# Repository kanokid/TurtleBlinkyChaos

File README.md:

# TurtleBlinkyChaos
This is a PCB design in the shape of a turtle that uses three astable multivibrators and SPDT switches to create a chaos blinky with two LEDs for the eyes that blink on and off, on and off, in kind of a random order depending on how you flip the switches.

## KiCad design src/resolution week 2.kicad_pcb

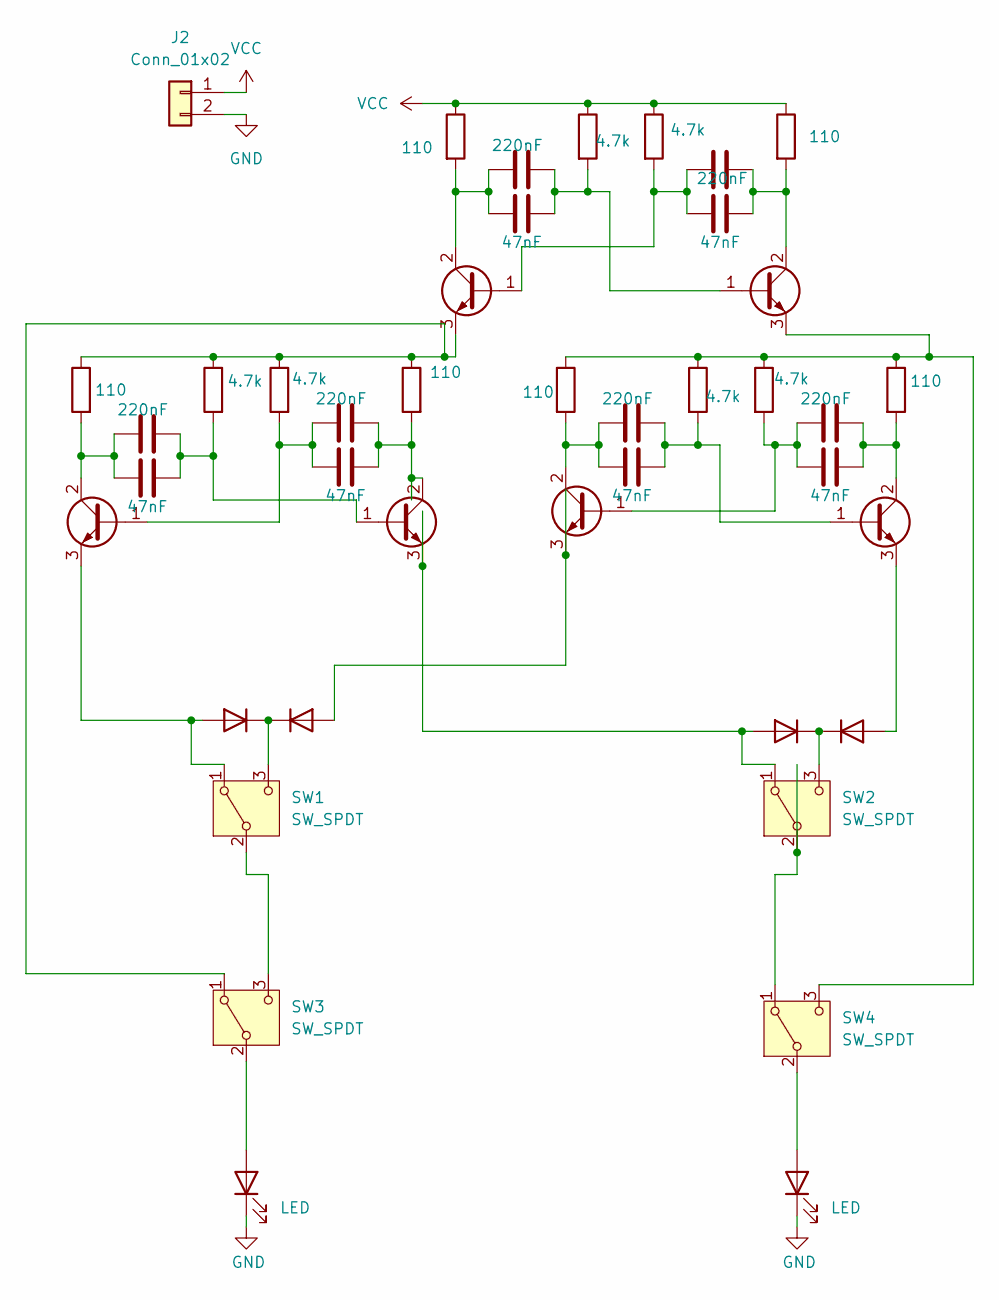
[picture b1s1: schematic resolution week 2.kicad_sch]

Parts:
C1, C2, C3, C4, C5, C6: 220nF; C_Disc_D5.0mm_W2.5mm_P5.00mm
C7, C8, C9, C10, C11, C12: 47nF; C_Disc_D5.0mm_W2.5mm_P5.00mm
D1, D3, D5, D6: D; D_DO-35_SOD27_P7.62mm_Horizontal
D4, D7: LED; LED_D5.0mm
J2: Conn_01x02; PinHeader_1x02_P2.54mm_Vertical
Q1, Q2, Q3, Q4, Q5, Q6: Q_NPN_BCE; TO-92L_Inline_Wide
R1, R4, R5, R8, R9, R12: 110; R_Axial_DIN0204_L3.6mm_D1.6mm_P7.62mm_Horizontal
R2, R3, R6, R7, R10, R11: 4.7k; R_Axial_DIN0204_L3.6mm_D1.6mm_P7.62mm_Horizontal
SW1, SW2, SW3, SW4: SW_SPDT; SS12D10G5

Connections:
GND: D4.1 (K), D7.1 (K), J2.2
unnamed: D1.2 (A), Q6.3 (E)
unnamed: D1.1 (K), D3.1 (K), SW1.3 (C)
unnamed: D3.2 (A), Q4.3 (E), SW1.1 (A)
unnamed: D4.2 (A), SW3.2 (B)
unnamed: D5.2 (A), Q5.3 (E)
unnamed: D5.1 (K), D6.1 (K), SW2.3 (C)
unnamed: D6.2 (A), Q3.3 (E), SW2.1 (A)
unnamed: D7.2 (A), SW4.2 (B)
unnamed: C1.1, C12.2, Q1.1 (B), R2.2
unnamed: C2.1, C11.2, Q1.2 (C), R4.2
unnamed: Q1.3 (E), R9.1, R10.1, R11.1, R12.1, SW4.3 (C)
unnamed: C2.2, C11.1, Q2.1 (B), R3.2
unnamed: C1.2, C12.1, Q2.2 (C), R1.2
unnamed: Q2.3 (E), R5.1, R6.1, R7.1, R8.1, SW3.1 (A)
unnamed: C4.1, C7.2, Q3.1 (B), R7.2
unnamed: C3.1, C8.2, Q3.2 (C), R5.2
unnamed: C3.2, C8.1, Q4.1 (B), R6.2
unnamed: C4.2, C7.1, Q4.2 (C), R8.2
unnamed: C6.1, C9.2, Q5.1 (B), R11.2
unnamed: C5.1, C10.2, Q5.2 (C), R9.2
unnamed: C5.2, C10.1, Q6.1 (B), R10.2
unnamed: C6.2, C9.1, Q6.2 (C), R12.2
unnamed: SW1.2 (B), SW3.3 (C)
unnamed: SW2.2 (B), SW4.1 (A)
VCC: J2.1, R1.1, R2.1, R3.1, R4.1

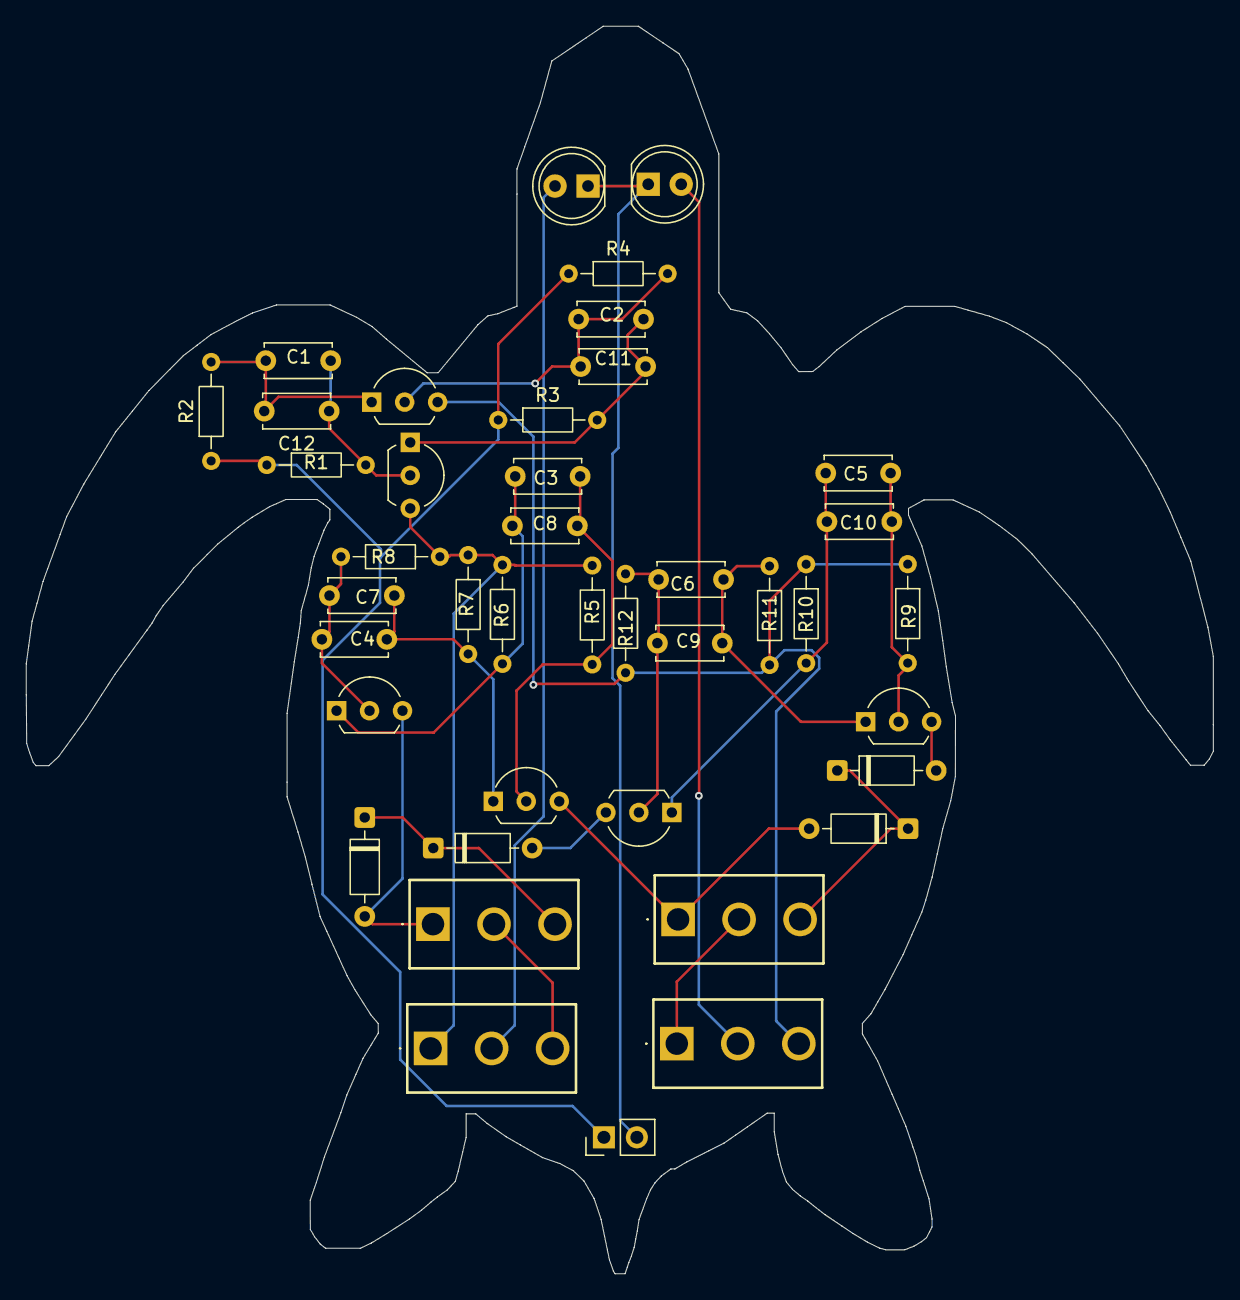
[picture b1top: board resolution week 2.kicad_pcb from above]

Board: 2 copper layers, 91.4 x 96.1 mm, 41 parts (0 on the bottom side), 26 nets.

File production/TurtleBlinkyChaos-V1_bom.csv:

Designator,Footprint,Quantity,Value,LCSC Part #
"C1, C2, C3, C4, C5, C6",C_Disc_D5.0mm_W2.5mm_P5.00mm,6,220nF,
"C10, C11, C12, C7, C8, C9",C_Disc_D5.0mm_W2.5mm_P5.00mm,6,47nF,
"D1, D3, D5, D6",D_DO-35_SOD27_P7.62mm_Horizontal,4,D,
"D4, D7",LED_D5.0mm,2,LED,
J2,PinHeader_1x02_P2.54mm_Vertical,1,Conn_01x02,
"Q1, Q2, Q3, Q4, Q5, Q6",TO-92L_Inline_Wide,6,Q_NPN_BCE,
"R1, R12, R4, R5, R8, R9",R_Axial_DIN0204_L3.6mm_D1.6mm_P7.62mm_Horizontal,6,110,
"R10, R11, R2, R3, R6, R7",R_Axial_DIN0204_L3.6mm_D1.6mm_P7.62mm_Horizontal,6,4.7k,
"SW1, SW2, SW3, SW4",SS12D10G5,4,SW_SPDT,

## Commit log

2026-03-25 added files
2026-03-25 added more stuff
